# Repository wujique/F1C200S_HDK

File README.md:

## 说明

这是一个F1C200S小板的原理图和PCB。

挖坑网：https://whycan.cn/t_3688.html

用KiCAD 5.1.5绘制。

库基于WJQ，其他器件和封装是KiCAD自带库。

WJQ库：https://github.com/wujique/KiCAD_Lib

gerber目录是投板文件。

bom目录是器件丝印和资料，用InteractiveHtmlBom生成。

**2020-02-29**

已经验证：

USB下载固件到SPI FLASH能启动，TTL能进控制台，RGB LCD能显示、触摸屏。

可以从TF卡启动。

未验证：

TV和音频输出、外扩接口。

如有需要，请联系：www.wujique.com

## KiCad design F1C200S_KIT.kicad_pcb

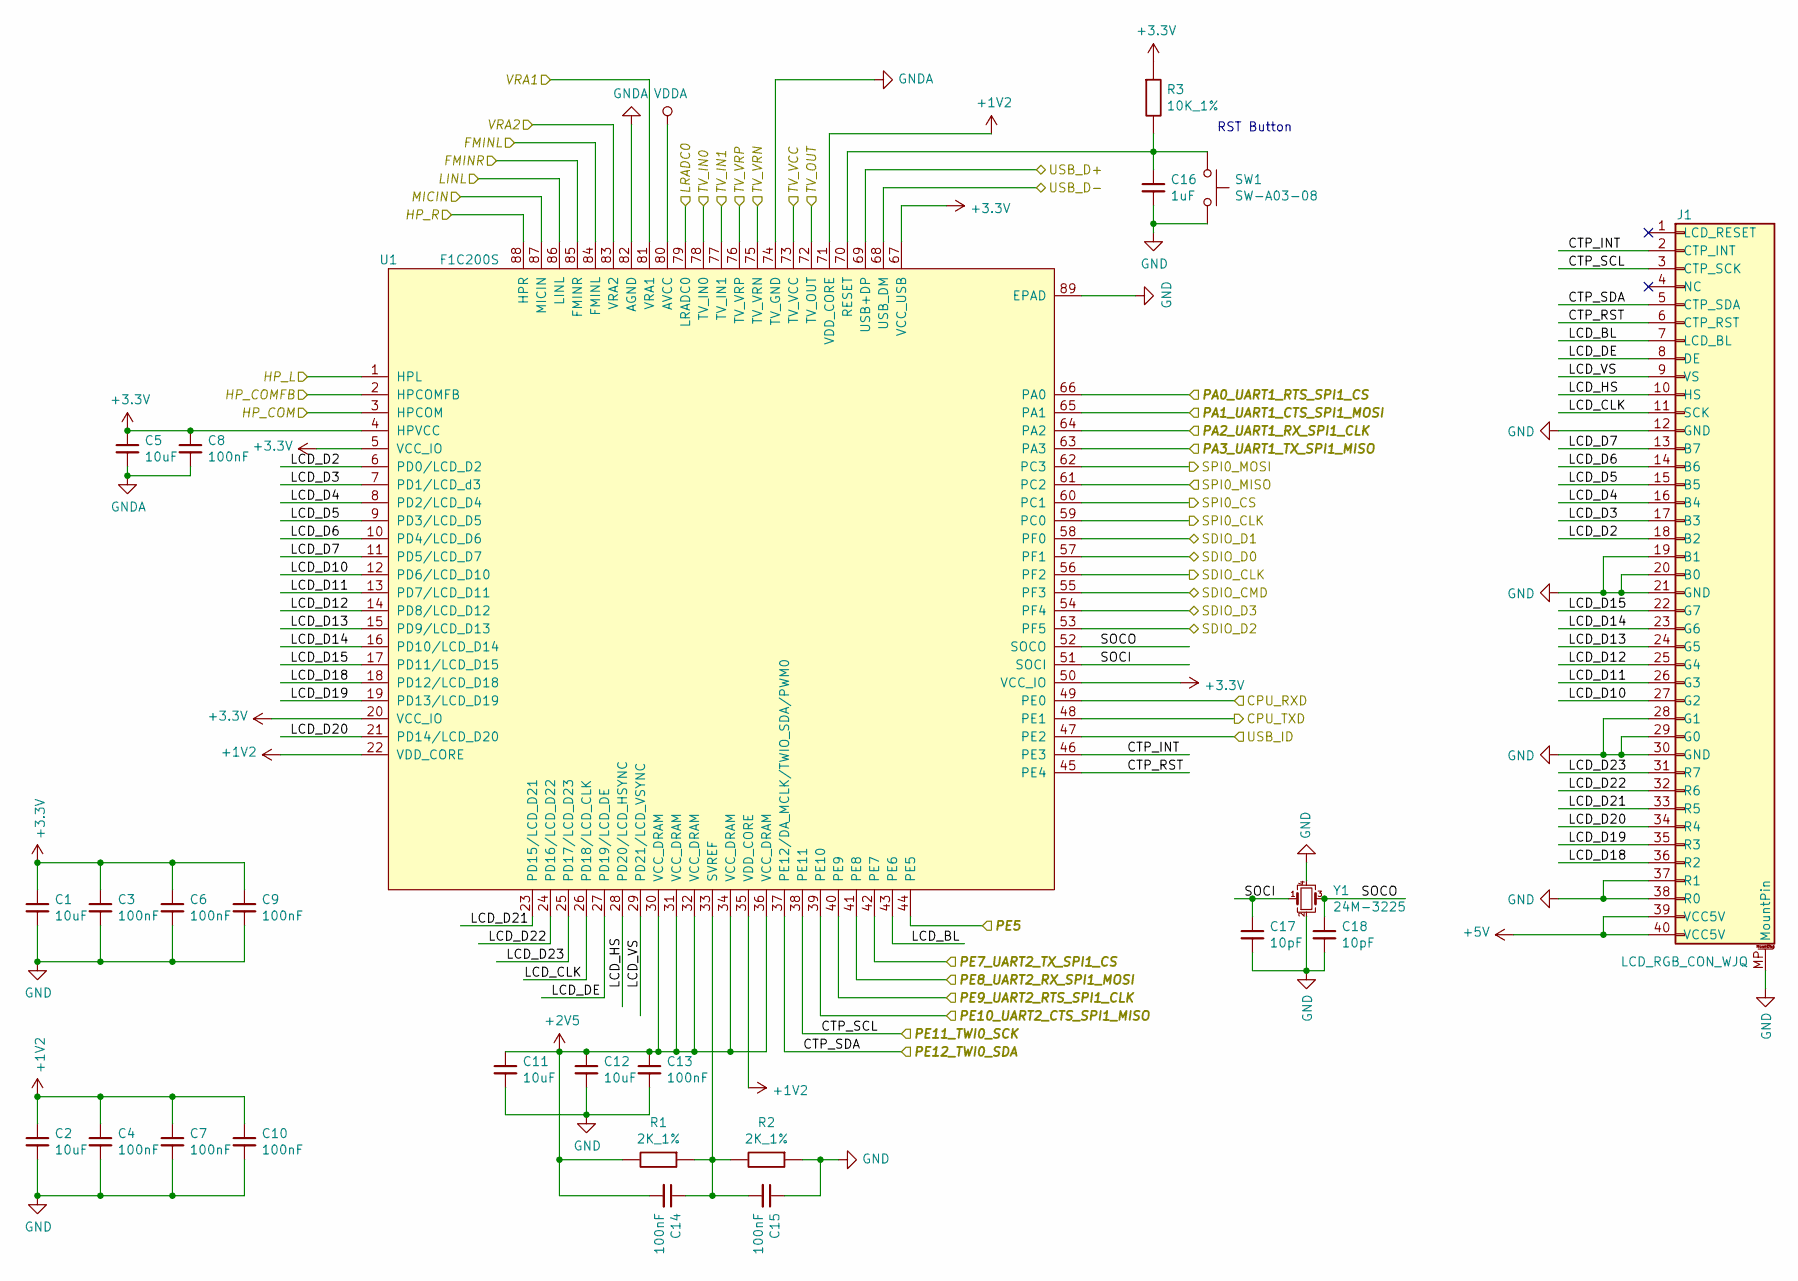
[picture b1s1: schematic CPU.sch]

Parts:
C1, C2, C5, C11, C12: 03.4004_C0603_10uF; C_0603_WJQ
C3, C4, C6, C7, C8, C9, C10, C13, C14, C15: 03.0009_C0402_100nF; C_0402_WJQ
C16: 03.0001_C0402_1uF; C_0402_WJQ
C17, C18: 03.0003_C0402_10pF; C_0402_WJQ
J1: 10.0402_LCD_RGB_CON_WJQ; FPC_40_0.5_BR
R1, R2: 02.0026_R0402_2K_1%; R_0402_WJQ
R3: 02.0008_R0402_10K_1%; R_0402_WJQ
SW1: 11.0101_SW-A03-08; SW_Push_Button__A03-08
U1: 08.0001_F1C200S; QFN-88_EP_10x10_Pitch0.4mm
Y1: 07.0403_Crystal_24M_3225; Crystal_SMD_3225-4Pin_3.2x2.5mm

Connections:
+1V2: C2.1, C4.1, C7.1, C10.1, U1.22 (VDD_CORE), U1.35 (VDD_CORE), U1.71 (VDD_CORE); also elsewhere on the board
+2V5: C11.1, C12.1, C13.1, C14.2, R1.2, U1.30 (VCC_DRAM), U1.31 (VCC_DRAM), U1.32 (VCC_DRAM), U1.34 (VCC_DRAM), U1.36 (VCC_DRAM); also elsewhere on the board
+5V: J1.39 (VCC5V), J1.40 (VCC5V); also elsewhere on the board
/CPU/CPU_RXD: U1.49 (PE0); also elsewhere on the board
/CPU/CPU_TXD: U1.48 (PE1); also elsewhere on the board
/CPU/CTP_INT: J1.2 (CTP_INT), U1.46 (PE3)
/CPU/CTP_RST: J1.6 (CTP_RST), U1.45 (PE4)
/CPU/FMINL: U1.84 (FMINL); also elsewhere on the board
/CPU/FMINR: U1.85 (FMINR); also elsewhere on the board
/CPU/HP_COM: U1.3 (HPCOM); also elsewhere on the board
/CPU/HP_COMFB: U1.2 (HPCOMFB); also elsewhere on the board
/CPU/HP_L: U1.1 (HPL); also elsewhere on the board
/CPU/HP_R: U1.88 (HPR); also elsewhere on the board
/CPU/LCD_BL: J1.7 (LCD_BL), U1.43 (PE6)
/CPU/LCD_CLK: J1.11 (SCK), U1.26 (PD18/LCD_CLK)
/CPU/LCD_D2: J1.18 (B2), U1.6 (PD0/LCD_D2)
/CPU/LCD_D3: J1.17 (B3), U1.7 (PD1/LCD_d3)
/CPU/LCD_D4: J1.16 (B4), U1.8 (PD2/LCD_D4)
/CPU/LCD_D5: J1.15 (B5), U1.9 (PD3/LCD_D5)
/CPU/LCD_D6: J1.14 (B6), U1.10 (PD4/LCD_D6)
/CPU/LCD_D7: J1.13 (B7), U1.11 (PD5/LCD_D7)
/CPU/LCD_D10: J1.27 (G2), U1.12 (PD6/LCD_D10)
/CPU/LCD_D11: J1.26 (G3), U1.13 (PD7/LCD_D11)
/CPU/LCD_D12: J1.25 (G4), U1.14 (PD8/LCD_D12)
/CPU/LCD_D13: J1.24 (G5), U1.15 (PD9/LCD_D13)
/CPU/LCD_D14: J1.23 (G6), U1.16 (PD10/LCD_D14)
/CPU/LCD_D15: J1.22 (G7), U1.17 (PD11/LCD_D15)
/CPU/LCD_D18: J1.36 (R2), U1.18 (PD12/LCD_D18)
/CPU/LCD_D19: J1.35 (R3), U1.19 (PD13/LCD_D19)
/CPU/LCD_D20: J1.34 (R4), U1.21 (PD14/LCD_D20)
/CPU/LCD_D21: J1.33 (R5), U1.23 (PD15/LCD_D21)
/CPU/LCD_D22: J1.32 (R6), U1.24 (PD16/LCD_D22)
/CPU/LCD_D23: J1.31 (R7), U1.25 (PD17/LCD_D23)
/CPU/LCD_DE: J1.8 (DE), U1.27 (PD19/LCD_DE)
/CPU/LCD_HS: J1.10 (HS), U1.28 (PD20/LCD_HSYNC)
/CPU/LCD_VS: J1.9 (VS), U1.29 (PD21/LCD_VSYNC)
/CPU/LINL: U1.86 (LINL); also elsewhere on the board
/CPU/LRADC0: U1.79 (LRADC0); also elsewhere on the board
/CPU/MICIN: U1.87 (MICIN); also elsewhere on the board
/CPU/PA0_UART1_RTS_SPI1_CS: U1.66 (PA0); also elsewhere on the board
/CPU/PA1_UART1_CTS_SPI1_MOSI: U1.65 (PA1); also elsewhere on the board
/CPU/PA2_UART1_RX_SPI1_CLK: U1.64 (PA2); also elsewhere on the board
/CPU/PA3_UART1_TX_SPI1_MISO: U1.63 (PA3); also elsewhere on the board
/CPU/PE5: U1.44 (PE5); also elsewhere on the board
/CPU/PE7_UART2_TX_SPI1_CS: U1.42 (PE7); also elsewhere on the board
/CPU/PE8_UART2_RX_SPI1_MOSI: U1.41 (PE8); also elsewhere on the board
/CPU/PE9_UART2_RTS_SPI1_CLK: U1.40 (PE9); also elsewhere on the board
/CPU/PE10_UART2_CTS_SPI1_MISO: U1.39 (PE10); also elsewhere on the board
/CPU/PE11_TWI0_SCK: J1.3 (CTP_SCK), U1.38 (PE11); also elsewhere on the board
/CPU/PE12_TWI0_SDA: J1.5 (CTP_SDA), U1.37 (PE12/DA_MCLK/TWIO_SDA/PWM0); also elsewhere on the board
/CPU/SDIO_CLK: U1.56 (PF2); also elsewhere on the board
/CPU/SDIO_CMD: U1.55 (PF3); also elsewhere on the board
/CPU/SDIO_D0: U1.57 (PF1); also elsewhere on the board
/CPU/SDIO_D1: U1.58 (PF0); also elsewhere on the board
/CPU/SDIO_D2: U1.53 (PF5); also elsewhere on the board
/CPU/SDIO_D3: U1.54 (PF4); also elsewhere on the board
/CPU/SOCI: C17.1, U1.51 (SOCI), Y1.1
/CPU/SOCO: C18.1, U1.52 (SOCO), Y1.3
/CPU/SPI0_CLK: U1.59 (PC0); also elsewhere on the board
/CPU/SPI0_CS: U1.60 (PC1); also elsewhere on the board
/CPU/SPI0_MISO: U1.61 (PC2); also elsewhere on the board
/CPU/SPI0_MOSI: U1.62 (PC3); also elsewhere on the board
/CPU/TV_IN0: U1.78 (TV_IN0); also elsewhere on the board
/CPU/TV_IN1: U1.77 (TV_IN1); also elsewhere on the board
/CPU/TV_OUT: U1.72 (TV_OUT); also elsewhere on the board
/CPU/TV_VCC: U1.73 (TV_VCC); also elsewhere on the board
/CPU/TV_VRN: U1.75 (TV_VRN); also elsewhere on the board
/CPU/TV_VRP: U1.76 (TV_VRP); also elsewhere on the board
/CPU/USB_D+: U1.69 (USB+DP); also elsewhere on the board
/CPU/USB_D-: U1.68 (USB_DM); also elsewhere on the board
/CPU/USB_ID: U1.47 (PE2); also elsewhere on the board
/CPU/VRA1: U1.81 (VRA1); also elsewhere on the board
/CPU/VRA2: U1.83 (VRA2); also elsewhere on the board
GND: C1.2, C2.2, C3.2, C4.2, C6.2, C7.2, C9.2, C10.2, C11.2, C12.2, C13.2, C15.1, C16.2, C17.2, C18.2, J1.12 (GND), J1.19 (B1), J1.20 (B0), J1.21 (GND), J1.28 (G1), J1.29 (G0), J1.30 (GND), J1.37 (R1), J1.38 (R0), J1.MP (MountPin), R2.1, SW1.2, U1.89 (EPAD), Y1.2, Y1.4; also elsewhere on the board
GNDA: C5.2, C8.2, U1.74 (TV_GND), U1.82 (AGND); also elsewhere on the board
unnamed: C14.1, C15.2, R1.1, R2.2, U1.33 (SVREF)
unnamed: C16.1, R3.2, SW1.1, U1.70 (RESET)
VDDA: U1.80 (AVCC); also elsewhere on the board

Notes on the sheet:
RST Button

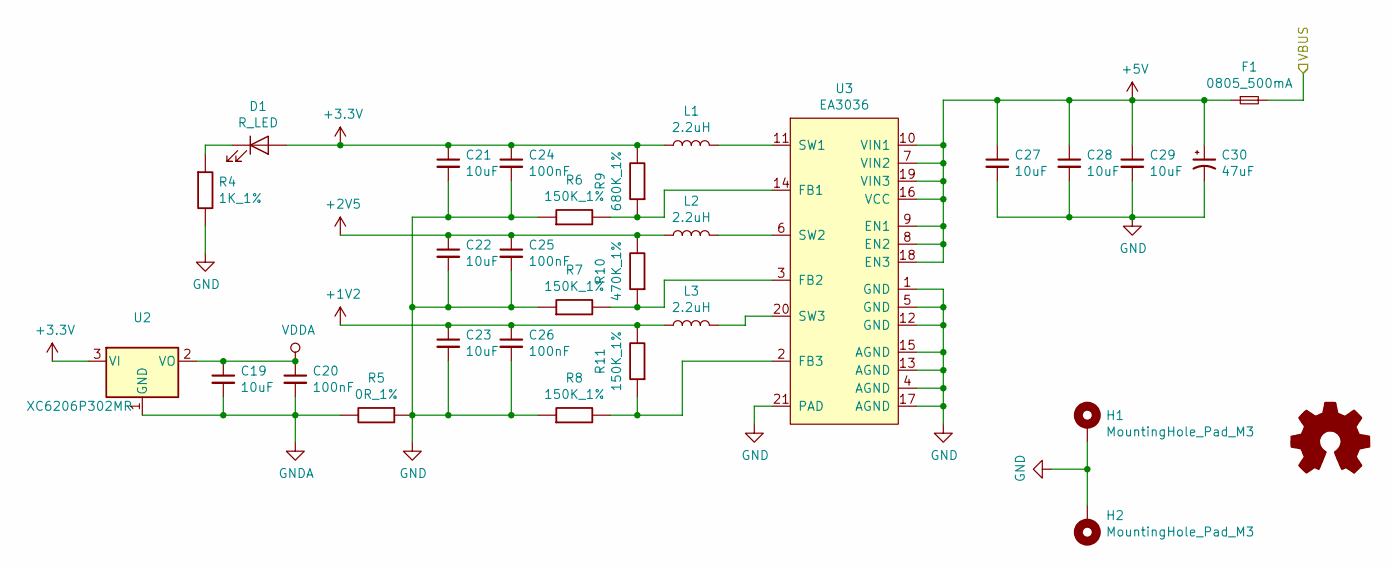
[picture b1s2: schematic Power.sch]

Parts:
C19, C21, C22, C23, C27, C28, C29: 03.4004_C0603_10uF; C_0603_WJQ
C20, C24, C25, C26: 03.0009_C0402_100nF; C_0402_WJQ
C30: 04.0002_CP1210_47uF; CP_EIA-3528-21_Kemet-B
D1: 07.0201_LED_Red_0603; LED_0603_1608Metric
F1: 07.0004_Fuse_0805_500mA; Fuse_0805_2012Metric
H1, H2: MountingHole_Pad_M3; MP_HOLE_L4_M3
L1, L2, L3: 06.0102_L2520_2.2uH; L_1008_2520_WJQ
LOGO1: Logo_Open_Hardware_Small; KiCad-Logo2_6mm_SilkScreen
R4: 02.0003_R0402_1K_1%; R_0402_WJQ
R5: 02.0001_R0402_0R_1%; R_0402_WJQ
R6, R7, R8, R11: 02.0023_R0402_150K_1%; R_0402_WJQ
R9: 02.0025_R0402_680K_1%; R_0402_WJQ
R10: 02.0024_R0402_470K_1%; R_0402_WJQ
U2: 09.0103_XC6206; SOT-23
U3: 09.0102_EA3036; QFN-20_EP_3x3_Pitch0.4mm

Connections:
+1V2: C23.1, C26.1, L3.1, R11.2; also elsewhere on the board
+2V5: C22.1, C25.1, L2.1, R10.2; also elsewhere on the board
+5V: C27.1, C28.1, C29.1, C30.1, F1.1, U3.7 (VIN2), U3.8 (EN2), U3.9 (EN1), U3.10 (VIN1), U3.16 (VCC), U3.18 (EN3), U3.19 (VIN3); also elsewhere on the board
/Misc/VBUS: F1.2; also elsewhere on the board
GND: C21.2, C22.2, C23.2, C24.2, C25.2, C26.2, C27.2, C28.2, C29.2, C30.2, H1.1, H2.1, R4.2, R5.1, R6.1, R7.1, R8.1, U3.1 (GND), U3.4 (AGND), U3.5 (GND), U3.12 (GND), U3.13 (AGND), U3.15 (AGND), U3.17 (AGND), U3.21 (PAD); also elsewhere on the board
GNDA: C19.2, C20.2, R5.2, U2.1 (GND); also elsewhere on the board
unnamed: D1.1 (K), R4.1
unnamed: L1.2, U3.11 (SW1)
unnamed: L2.2, U3.6 (SW2)
unnamed: L3.2, U3.20 (SW3)
unnamed: R6.2, R9.1, U3.14 (FB1)
unnamed: R7.2, R10.1, U3.3 (FB2)
unnamed: R8.2, R11.1, U3.2 (FB3)
VDDA: C19.1, C20.1, U2.2 (VO); also elsewhere on the board

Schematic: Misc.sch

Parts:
C31: 03.0011_C0603_1uF; C_0603_1608Metric
C33: 03.0012_C0603_2.2uF; C_0603_1608Metric
C34, C36, C37: 03.0009_C0402_100nF; C_0402_1005Metric
D3, D4, D5: 07.0002_D_TVS_PESDNC2FD5VB; DFN1006-2L
J2, J5: 10.0002_USB_Micro; MicroUSB_5S_B_A01SB141B1-067
J3: 10.0001_Micro_SD_Card; microSD_HRO_TF_01A
J4: 10.0201_PH2X15_2D54_V; PinHeader_2x15_P2.54mm_Vertical
R13, R14, R15, R16, R17: 02.0014_R0402_47K_1%; R_0402_1005Metric
R18: 02.0005_R0402_4K7_1%; R_0402_1005Metric
R19, R20: 02.0008_R0402_10K_1%; R_0402_1005Metric
U4: 09.0001_CP2104; QFN-24-1EP_4x4mm_P0.5mm_EP2.6x2.6mm
U5: 09.0303_GD5F1GQ4; WSON-8-1EP_8x6mm_P1.27mm_EP3.4x4.3mm
U6: 09.0302_W25Q128JVS; SOIC-8_5.23x5.23mm_P1.27mm

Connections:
+5V: J4.12, J4.14; also elsewhere on the board
/CPU/CPU_RXD: U4.21 (TXD); also elsewhere on the board
/CPU/CPU_TXD: U4.20 (RXD); also elsewhere on the board
/CPU/PA0_UART1_RTS_SPI1_CS: J4.1; also elsewhere on the board
/CPU/PA1_UART1_CTS_SPI1_MOSI: J4.6; also elsewhere on the board
/CPU/PA2_UART1_RX_SPI1_CLK: J4.9; also elsewhere on the board
/CPU/PA3_UART1_TX_SPI1_MISO: J4.10; also elsewhere on the board
/CPU/PE5: J4.5; also elsewhere on the board
/CPU/PE7_UART2_TX_SPI1_CS: J4.15; also elsewhere on the board
/CPU/PE8_UART2_RX_SPI1_MOSI: J4.22; also elsewhere on the board
/CPU/PE9_UART2_RTS_SPI1_CLK: J4.19; also elsewhere on the board
/CPU/PE10_UART2_CTS_SPI1_MISO: J4.17; also elsewhere on the board
/CPU/PE11_TWI0_SCK: J4.27; also elsewhere on the board
/CPU/PE12_TWI0_SDA: J4.28; also elsewhere on the board
/CPU/SDIO_CLK: J3.5 (CLK); also elsewhere on the board
/CPU/SDIO_CMD: J3.3 (CMD), R15.2; also elsewhere on the board
/CPU/SDIO_D0: J3.7 (DAT0), R14.2; also elsewhere on the board
/CPU/SDIO_D1: J3.8 (DAT1), R13.2; also elsewhere on the board
/CPU/SDIO_D2: J3.1 (DAT2), R17.2; also elsewhere on the board
/CPU/SDIO_D3: J3.2 (DAT3/CD), R16.2; also elsewhere on the board
/CPU/SPI0_CLK: J4.4, U5.6 (SCLK), U6.6 (CLK); also elsewhere on the board
/CPU/SPI0_CS: J4.11, R19.1, U5.1 (CS), U6.1 (~CS); also elsewhere on the board
/CPU/SPI0_MISO: J4.2, U5.2 (SO), U6.2 (DO(IO1)); also elsewhere on the board
/CPU/SPI0_MOSI: J4.3, U5.5 (SI), U6.5 (DI(IO0)); also elsewhere on the board
/CPU/USB_D+: D3.1 (A1), J5.3 (D+); also elsewhere on the board
/CPU/USB_D-: D4.1 (A1), J5.2 (D-); also elsewhere on the board
/CPU/USB_ID: D5.1 (A1), J5.4 (ID), R20.2; also elsewhere on the board
/Misc/CP2104_RST: C33.2, C34.2, R18.2, U4.5 (VIO), U4.6 (VDD)
/Misc/VBUS: C31.2, J2.1 (VBUS), J5.1 (VBUS), U4.7 (REGIN), U4.8 (VBUS); also elsewhere on the board
GND: C31.1, C33.1, C34.1, C36.2, C37.2, D3.2 (A2), D4.2 (A2), D5.2 (A2), J2.5 (GND), J2.6 (Shield), J3.6 (VSS), J3.10 (SHIELD), J4.8, J4.13, J4.21, J4.23, J4.30, J5.5 (GND), J5.6 (Shield), U4.2 (GND), U4.25 (PAD), U5.4 (VSS), U5.9 (EP), U6.4 (GND); also elsewhere on the board
unnamed: J2.2 (D-), U4.4 (D-)
unnamed: J2.3 (D+), U4.3 (D+)
unnamed: R18.1, U4.9 (~RST)

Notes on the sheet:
Note: add tvs
SPI NOR Flash
SD NAND/JTAG/WIFI/TF CARD
PCB edge
SPI NAND Flash

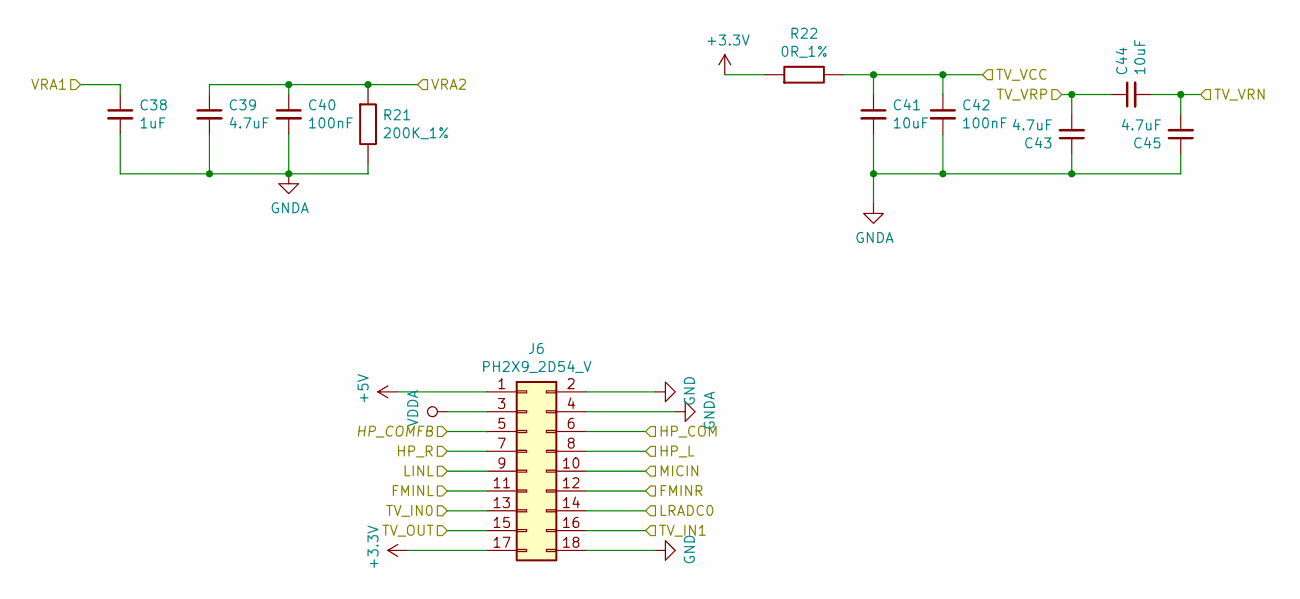
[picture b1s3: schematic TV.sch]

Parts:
C38: 03.0001_C0402_1uF; C_0402_WJQ
C39, C43, C45: 03.4003_C0603_4.7uF; C_0603_WJQ
C40, C42: 03.0009_C0402_100nF; C_0402_WJQ
C41: 03.4004_C0603_10uF; C_0603_WJQ
C44: 03.0016_C0603_10uF; C_0603_1608Metric
J6: 10.0202_PH2X9_2D54_V; PinHeader_2x09_P2.54mm_Vertical
R21: 02.0027_R0402_200K_1%; R_0402_WJQ
R22: 02.0001_R0402_0R_1%; R_0402_WJQ

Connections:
+5V: J6.1; also elsewhere on the board
/CPU/FMINL: J6.11; also elsewhere on the board
/CPU/FMINR: J6.12; also elsewhere on the board
/CPU/HP_COM: J6.6; also elsewhere on the board
/CPU/HP_COMFB: J6.5; also elsewhere on the board
/CPU/HP_L: J6.8; also elsewhere on the board
/CPU/HP_R: J6.7; also elsewhere on the board
/CPU/LINL: J6.9; also elsewhere on the board
/CPU/LRADC0: J6.14; also elsewhere on the board
/CPU/MICIN: J6.10; also elsewhere on the board
/CPU/TV_IN0: J6.13; also elsewhere on the board
/CPU/TV_IN1: J6.16; also elsewhere on the board
/CPU/TV_OUT: J6.15; also elsewhere on the board
/CPU/TV_VCC: C41.1, C42.1, R22.2; also elsewhere on the board
/CPU/TV_VRN: C44.2, C45.2; also elsewhere on the board
/CPU/TV_VRP: C43.2, C44.1; also elsewhere on the board
/CPU/VRA1: C38.1; also elsewhere on the board
/CPU/VRA2: C39.1, C40.1, R21.1; also elsewhere on the board
GND: J6.2, J6.18; also elsewhere on the board
GNDA: C38.2, C39.2, C40.2, C41.2, C42.2, C43.1, C45.1, J6.4, R21.2; also elsewhere on the board
VDDA: J6.3; also elsewhere on the board

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
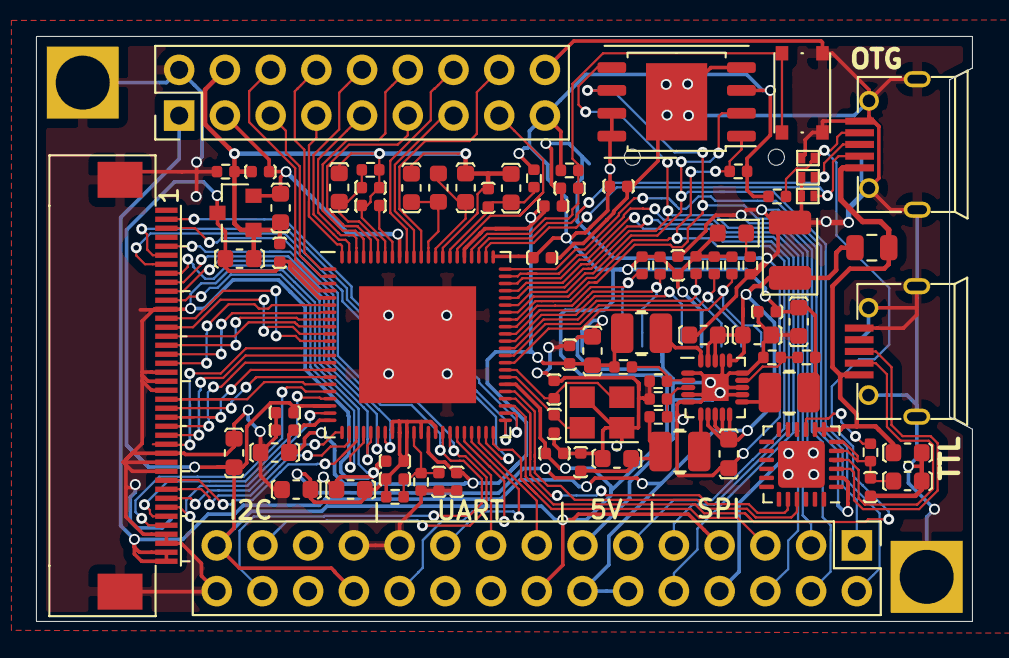
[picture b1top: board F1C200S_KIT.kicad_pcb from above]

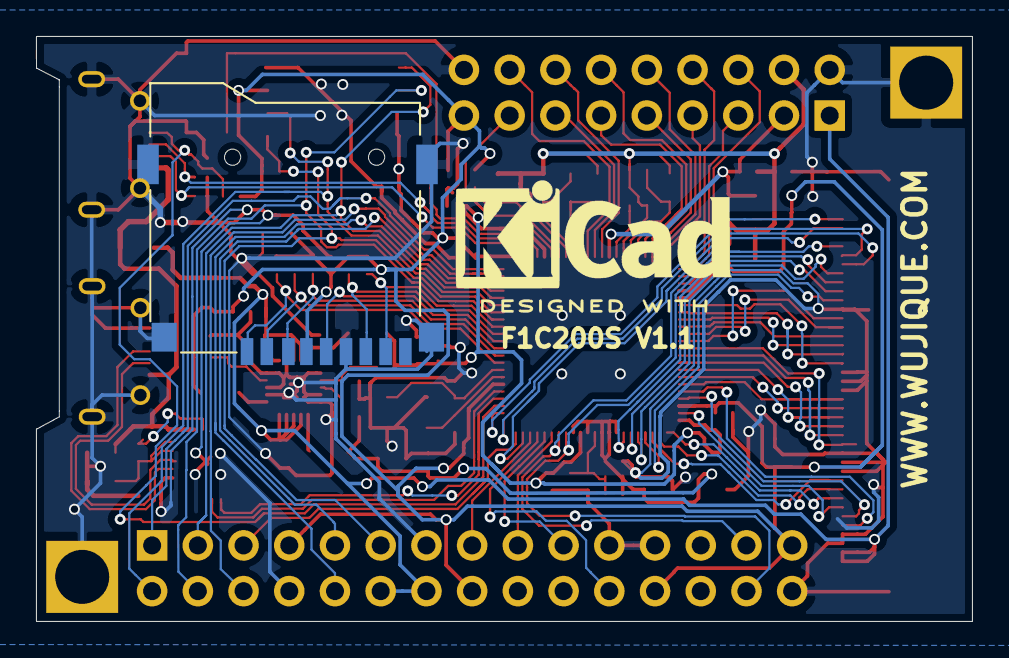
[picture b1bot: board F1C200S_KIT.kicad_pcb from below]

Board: 2 copper layers, 52.0 x 32.5 mm, 89 parts (2 on the bottom side), 91 nets.

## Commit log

2020-02-11 绘制完成，未投板验证
2020-02-11 modify readme.md
2020-02-11 修改边框，出gerber，添加pdf格式原理图
2020-02-12 修改BOM，添加TF卡和USB、按键的购买链接
2020-02-12 增加器件库链接
2020-02-16 修改XC6206信息，明确型号为3.0V输出
2020-02-25 修改README, 板子大部分功能已经验证
2020-02-29 触摸屏已经验证，修改readme
2020-03-07 增加挖坑网连接
2020-03-29 优化封装外形丝印，PCB进行拼板处理
2020-03-29 修改靠近板边的地线，解决锣板掏线问题
2021-02-11 remove .kicad_pcb-bak and .sch-bak files, and adding them to .gitignore.
